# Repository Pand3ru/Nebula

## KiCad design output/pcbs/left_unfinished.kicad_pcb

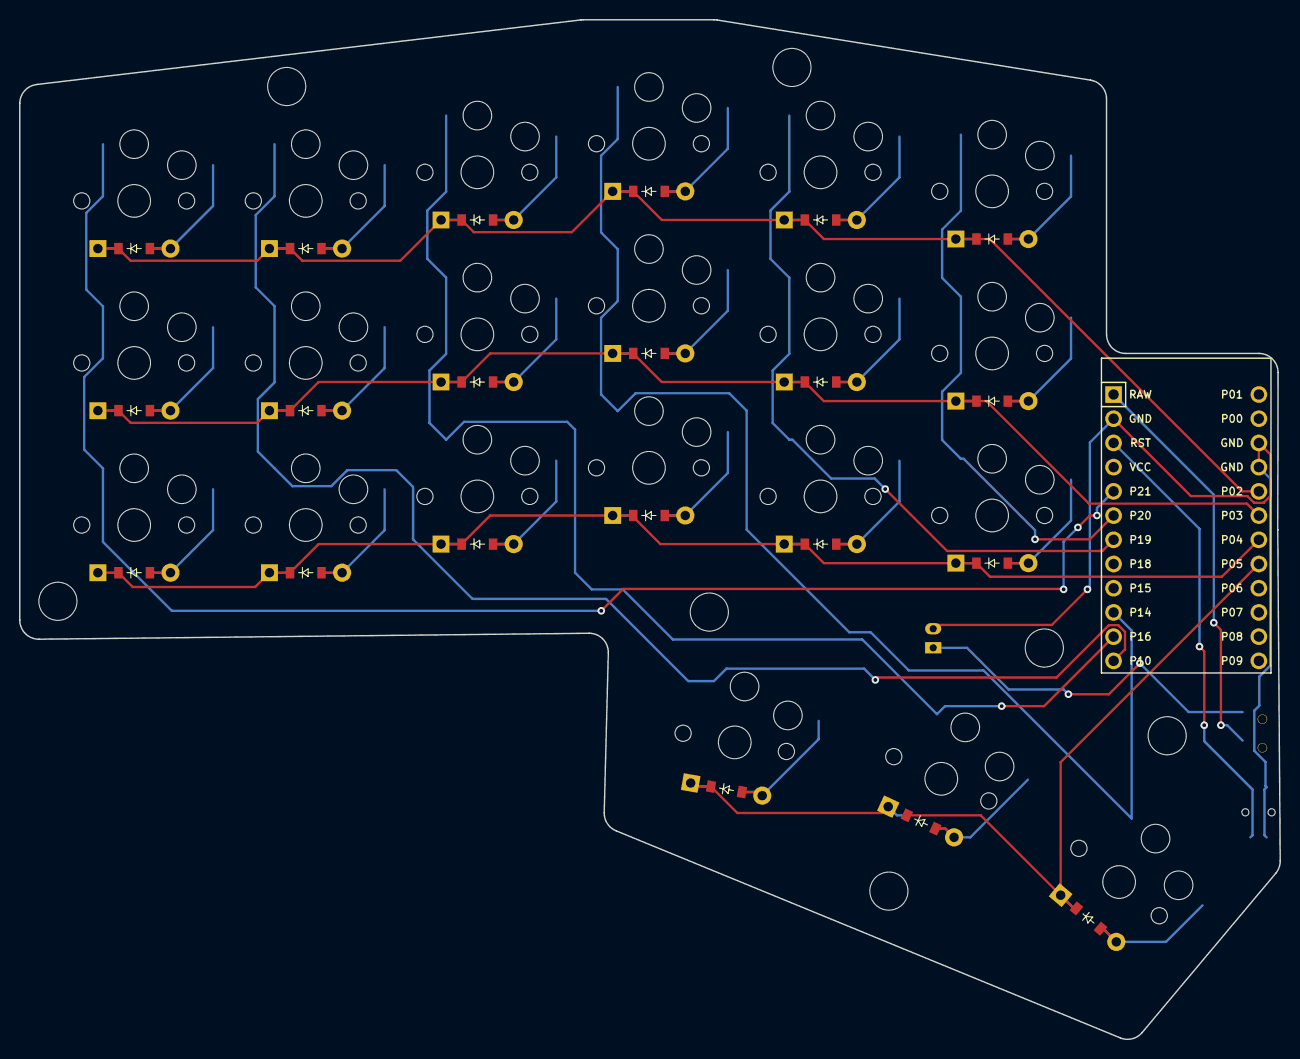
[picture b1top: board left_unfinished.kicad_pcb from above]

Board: 2 copper layers, 132.2 x 107.0 mm, 46 parts (0 on the bottom side), 35 nets.

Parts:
B1: Panasonic_EVQPUL_EVQPUC
D1, D2, D3, D4, D5, D6, D7, D8, D9, D10, D11, D12, D13, D14, D15, D16, D17, D18, D19, D20, D21: ComboDiode
JST1: JST_PH_S2B-PH-K_02x2.00mm_Angled
MCU1: ProMicro
S1, S2, S3, S4, S5, S6, S7, S8, S9, S10, S11, S12, S13, S14, S15, S16, S17, S18, S19, S20, S21: PG1350
T1: SPDT_C128955

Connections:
GND: B1.1, JST1.2, MCU1.2, MCU1.15, MCU1.16
P2: D3.1, D6.1, D9.1, D12.1, D15.1, D18.1, MCU1.17
P3: D2.1, D5.1, D8.1, D11.1, D14.1, D17.1, MCU1.18
P4: D1.1, D4.1, D7.1, D10.1, D13.1, D16.1, MCU1.19
P5: D19.1, D20.1, D21.1, MCU1.20
P10: MCU1.12, S4.1, S5.1, S6.1, S19.1
P14: MCU1.10, S10.1, S11.1, S12.1, S21.1
P16: MCU1.11, S7.1, S8.1, S9.1, S20.1
P19: MCU1.7, S13.1, S14.1, S15.1
P20: MCU1.6, S16.1, S17.1, S18.1
P21: MCU1.5, S1.1, S2.1, S3.1
RAW: MCU1.1, T1.2
RST: B1.2, MCU1.3
index_middle: D14.2, S14.2
index_under: D13.2, S13.2
index_upper: D15.2, S15.2
inner_middle: D17.2, S17.2
inner_under: D16.2, S16.2
inner_upper: D18.2, S18.2
left_row: D19.2, S19.2
mid_row: D20.2, S20.2
middle_middle: D11.2, S11.2
middle_under: D10.2, S10.2
middle_upper: D12.2, S12.2
outer_middle: D2.2, S2.2
outer_under: D1.2, S1.2
outer_upper: D3.2, S3.2
pinky_middle: D5.2, S5.2
pinky_under: D4.2, S4.2
pinky_upper: D6.2, S6.2
pos: JST1.1, T1.1
right_row: D21.2, S21.2
ring_middle: D8.2, S8.2
ring_under: D7.2, S7.2
ring_upper: D9.2, S9.2

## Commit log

2024-12-04 Init commit
